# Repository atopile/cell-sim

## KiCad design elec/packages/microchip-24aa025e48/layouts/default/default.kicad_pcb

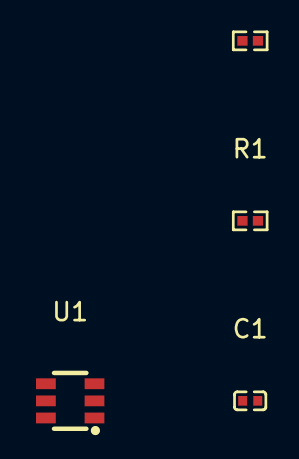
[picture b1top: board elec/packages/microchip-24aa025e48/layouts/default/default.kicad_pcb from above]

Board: 2 copper layers, 4 parts (0 on the bottom side), 4 nets, no tracks yet.

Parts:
C1: 100nF; C0402
R1, R2: 4.7kΩ; R0402
U1: SOT-23-6_L2.9-W1.6-P0.95-LS2.8-BR

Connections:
SCL: R1.1, U1.1
SDA: R2.1, U1.3
hv: C1.1, R1.2, R2.2, U1.6
lv: C1.2, U1.2, U1.4, U1.5

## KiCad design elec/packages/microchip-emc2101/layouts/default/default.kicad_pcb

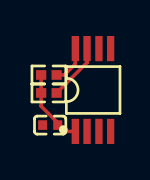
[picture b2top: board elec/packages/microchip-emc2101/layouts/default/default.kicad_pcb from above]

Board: 2 copper layers, 4 parts (0 on the bottom side), 4 nets.

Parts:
C1: 100nF; C0402
R1, R2: 10kΩ; R0402
U1: MSOP-8_L3.0-W3.0-P0.65-LS4.9-BL

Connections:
SCL: R1.1, U1.8
SDA: R2.1, U1.7
hv: C1.1, R1.2, R2.2, U1.1
lv: C1.2, U1.5

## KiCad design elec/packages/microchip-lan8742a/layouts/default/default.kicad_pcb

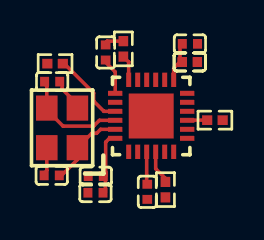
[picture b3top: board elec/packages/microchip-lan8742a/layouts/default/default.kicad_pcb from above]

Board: 2 copper layers, 15 parts (0 on the bottom side), 9 nets.

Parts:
C1, C2, C3, C4: 100nF; C0402
C5, C6: 1µF; C0402
C7: 470pF; C0402
C8, C9: 18pF; C0402
R1, R3: 100kΩ; R0402
R2: 12.1kΩ; R0402
R4: 10kΩ; R0402
U1: QFN-24_L4.0-W4.0-P0.50-TL-EP2.5
X1: OSC-SMD_4P-L3.2-W2.5-BL_SIT8008BI

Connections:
10: R1.1, U1.10
ETH_LED_LINK: R3.1, U1.3
RBIAS: R2.1, U1.24
decoupling_3v3_bulk-power-hv: C1.1, C2.1, C3.1, C4.1, C5.1, R4.2, U1.1, U1.9, U1.19
hv: C6.1, C7.1, U1.6
lv: C1.2, C2.2, C3.2, C4.2, C5.2, C6.2, C7.2, C8.2, C9.2, R1.2, R2.2, R3.2, U1.25, X1.2, X1.4
nRST: R4.1, U1.15
xtal_caps[0]-power-hv: C8.1, U1.5, X1.1
xtal_caps[1]-power-hv: C9.1, U1.4, X1.3

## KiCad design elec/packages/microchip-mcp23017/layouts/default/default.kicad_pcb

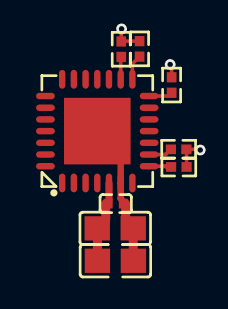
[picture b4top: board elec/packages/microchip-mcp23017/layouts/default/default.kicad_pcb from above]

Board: 2 copper layers, 9 parts (0 on the bottom side), 7 nets.

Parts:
C1: 100nF; C0402
C2, C3: 10µF; C0805
R1, R2, R3, R4, R5: 10kΩ; R0402
U1: QFN-28_L6.0-W6.0-P0.65-BL-EP3.7

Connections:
INTA: R2.1, U1.16
INTB: R3.1, U1.15
SCL: R4.1, U1.8
SDA: R5.1, U1.9
hv: C1.1, C2.1, C3.1, R1.2, R2.2, R3.2, R4.2, R5.2, U1.5
lv: C1.2, C2.2, C3.2, U1.6, U1.29
nRESET: R1.1, U1.14
